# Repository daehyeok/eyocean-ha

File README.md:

# eyocean-ha

ESPHome-based Home Assistant integration for the **EYOCEAN LED Desk Lamp** (ASIN: B0BNDLND3Y) via 433.92 MHz RF control.

The EYOCEAN desk lamp uses a 433.92 MHz ASK/OOK remote with an **EV1527-based** protocol (32-bit fixed codes — extended from standard 24-bit EV1527, no rolling code). This project replaces the physical remote with an ESP32 + CC1101 transceiver, giving full Home Assistant control.

## Hardware

| Component                          | Purpose         |
| ---------------------------------- | --------------- |
| ESP32-S3 DevKit                    | Microcontroller |
| CC1101 433MHz module (SMA antenna) | RF transceiver  |
| Dupont wires                       | Wiring          |
| USB-C cable + power adapter        | Power           |

An ESP32-S3 SuperMini can instead sit on the [carrier board](#carrier-board--enclosure-esp32-s3-supermini),
which replaces the Dupont wires and fits a 3D-printed case.

### Wiring (ESP32-S3)

```
ESP32-S3          CC1101
─────────         ──────
GPIO9  (CLK)  →   SCK
GPIO10 (MOSI) →   MOSI
GPIO11 (MISO) →   MISO
GPIO12 (CS)   →   CSN
GPIO13 (TX)   →   GDO0
GPIO14 (RX)   →   GDO2
3.3V          →   VCC
GND           →   GND
```

### Wiring (ESP32-C3 SuperMini)

```
ESP32-C3          CC1101
─────────         ──────
GPIO4  (SCK)  →   SCK
GPIO10 (MOSI) →   MOSI
GPIO3  (MISO) →   MISO
GPIO7  (CS)   →   CSN
GPIO1  (TX)   →   GDO0
GPIO2  (RX)   →   GDO2
3.3V          →   VCC
GND           →   GND
```

> [!CAUTION]
> CC1101 runs on 3.3V only. Do NOT connect to 5V.

### Carrier board + enclosure (ESP32-S3 SuperMini)

Instead of Dupont wires you can solder both modules straight onto a small
carrier PCB (`pcb/`) and close it in a 3D-printed box (`cad/`):

| Part                                                 | Qty | Notes                                                    |
| ---------------------------------------------------- | --- | -------------------------------------------------------- |
| Carrier PCB, 53.5 × 32 mm, 2 layers, 1.6 mm          | 1   | `pcb/production/eyocean_carrier_jlcpcb.zip`              |
| ESP32-S3 SuperMini                                   | 1   | male headers pointing down, soldered to the carrier      |
| CC1101 433 MHz module with SMA (see `CC1101_specs/`) | 1   | its male 2×4 header soldered to the carrier              |
| 10 µF capacitor, 0603, X5R, 10 V (LCSC C19702)       | 1   | on the back; CC1101 VDD bulk (module has its own 100 nF) |
| M2 × 16 flat-head (countersunk) bolt                 | 4   | flush; M2 × 14 / × 12 also work (counterbore)            |
| M2 hex nut                                           | 4   | captured under the base                                  |
| 433 MHz SMA antenna                                  | 1   | screws on outside the case                               |

No sockets are used: each module rests on its header's plastic spacer,
2.5 mm above the carrier. The CC1101's edge lines up with the board's SMA
end so the SMA barrel hangs past it.

The carrier routes the CC1101 to the SuperMini's **left** header column
(TX, RX, GPIO1–7). 3V3 and GND come from the right column; 5V is never
connected. GPIO3 is left free because it is a strapping / VBUS-sense pin on
some SuperMini clones.

| CC1101 pin | Signal    | SuperMini pin | ESPHome substitution |
| ---------- | --------- | ------------- | -------------------- |
| 1          | GND       | GND           | –                    |
| 2          | VDD       | 3V3           | –                    |
| 3          | GDO0      | GPIO7         | `pin_tx`             |
| 4          | CSN       | GPIO6         | `pin_cs`             |
| 5          | SCK       | GPIO5         | `pin_sck`            |
| 6          | MOSI      | GPIO4         | `pin_mosi`           |
| 7          | MISO/GDO1 | GPIO2         | `pin_miso`           |
| 8          | GDO2      | GPIO1         | `pin_rx`             |

`esphome/pzloz-carrier.yaml` already uses these pins. It includes
`eyocean-rf.yaml` and only overrides the name, the pins and your remote
codes, so it works for EYOCEAN lamps too.

**PCB.** The KiCad 10 project is generated from `pcb/scripts/board_def.py`
(one table for pins, placement and nets). `pcb/scripts/build.sh`
regenerates the schematic and the board, runs ERC and DRC (with schematic
parity) and exports the JLCPCB Gerber zip, SVGs, a 3D render and a STEP
model to `pcb/production/`. The board keeps copper out from under the
SuperMini's chip antenna (the far end, opposite the USB-C port).

**Enclosure.** A base and a lid, 60.5 × 37 × 18.1 mm, split on the SMA
axis. It has a USB-C opening, an SMA U-slot, WiFi slots over the antenna,
and four flush M2 × 16 bolts into hex nuts under the base. See
**[`cad/README.md`](cad/README.md)** for the build guide: prerequisites,
how every height is calculated, what to measure on your parts, export
commands, print settings and assembly.

```bash
git submodule update --init   # BOSL2
cad/export.sh                 # -> cad/export/enclosure_{bottom,lid}.{stl,3mf}
```

Assembly in short:

1. Solder the SuperMini (USB-C at the board edge) and
   the CC1101 (SMA end flush with the board edge), with header spacers flat
   on the carrier.
2. Trim the pin tails under the board to ≤ 2.5 mm, then solder the 10 µF
   capacitor on the back (it sits in the 3.5 mm gap above the case floor).
3. Drop the board into the base. The SMA thread goes into the U-slot.
4. Close the lid, push an M2 nut into each hex pocket under the base, and
   tighten the four bolts from the top.
5. Screw the 433 MHz antenna onto the SMA.

## Protocol Details

| Parameter       | Value                                                     |
| --------------- | --------------------------------------------------------- |
| Frequency       | 433.92 MHz                                                |
| Modulation      | ASK/OOK                                                   |
| Protocol        | EV1527-based (32-bit)                                     |
| Frame structure | 16-bit fixed prefix + 8-bit button code + 8-bit XOR check |
| Security        | Fixed code (no rolling)                                   |
| FCC ID          | 2BD2C-ZZ02DY01007                                         |

### Decoded Remote Codes

The EYOCEAN remote uses a **32-bit** frame (not standard 24-bit EV1527). All 32 bits are required — the lamp ignores truncated 24-bit frames.

**Frame structure:**

| Byte | Content       | Varies per remote?              |
| ---- | ------------- | ------------------------------- |
| 0-1  | Remote ID     | **yes** — per-remote address    |
| 2    | Function code | no — same across remotes        |
| 3    | Checksum      | `byte2 XOR key`, key per-remote |

```
code = (remote_id << 16) | (cmd << 8) | (cmd ^ xor_key)
```

The **function codes are shared across units** — only the 16-bit remote ID and the 8-bit XOR key are per-remote. This reproduces all 11 known codes from the two fully-decoded remotes below.

| Button            | Function code   |
| ----------------- | --------------- |
| Power On/Off      | `0x51`          |
| Brightness        | `0x5B`          |
| Color Temperature | `0x5A`          |
| Reading Mode      | `0x49`          |
| Night Light       | `0x41` / `0x4D` |
| Timer Function    | `0x4D` / `0x41` |

`0x41` and `0x4D` swap meaning between models: 5-button remotes (no timer) use `0x41` for night light, and the two 6-button remotes reported so far disagree with each other — see [#3](https://github.com/bl4ko/eyocean-ha/issues/3). If those two buttons act swapped on your lamp, exchange `cmd_night_light` / `cmd_timer` in the config.

**Known remotes:**

| Lamp                                | Remote ID | XOR key | Source                                                    |
| ----------------------------------- | --------- | ------- | --------------------------------------------------------- |
| EYOCEAN (ASIN B0BNDLND3Y), 5 buttons | `0xBAD1`  | `0x4E`  | this repo                                                  |
| EYOCEAN CLED-2600C (ASIN B09ZHYNYB9), 6 buttons | `0xDCCF` | `0x76` | [#3](https://github.com/bl4ko/eyocean-ha/issues/3) |
| Pzloz, 6 buttons                    | ?         | ?       | [#1](https://github.com/bl4ko/eyocean-ha/issues/1) (partial) |

The XOR key is not derivable from the remote ID with the data available (`0xBAD1`→`0x4E`, `0xDCCF`→`0x76`); treat it as an independent per-remote value.

> [!IMPORTANT]
> **You still need to capture one button from your own remote** to learn its ID and XOR key — but only one. Capture any button, then read the ID off bytes 0-1 and compute the key as `byte2 XOR byte3`; the other buttons follow from the formula. See [Capturing Your Own Codes](#capturing-your-own-codes). Standard 24-bit EV1527 decoders (Flipper Zero, rtl_433) only show the first 24 bits — you must capture raw data and decode all 32 bits.

## Installation

### 1. Configure

Everything unit-specific lives in the `substitutions:` block at the top of `esphome/eyocean-rf.yaml`:

```yaml
substitutions:
  board: esp32-s3-devkitc-1
  pin_sck: GPIO9
  pin_mosi: GPIO10
  pin_miso: GPIO11
  pin_cs: GPIO12
  pin_tx: GPIO13
  pin_rx: GPIO14

  remote_id: "0xBAD1"
  xor_key: "0x4E"
  cmd_night_light: "0x41"
  cmd_timer: "0x4D"
```

For an ESP32-C3 SuperMini, swap in:

```yaml
  board: esp32-c3-devkitm-1
  pin_sck: GPIO4
  pin_mosi: GPIO10
  pin_miso: GPIO3
  pin_cs: GPIO7
  pin_tx: GPIO1
  pin_rx: GPIO2
```

Set `remote_id` and `xor_key` from your own capture — see [Capturing Your Own Codes](#capturing-your-own-codes).

### Pzloz desk lamp (6 buttons)

Pzloz lamps use the same 32-bit protocol and function codes. Flash
`esphome/pzloz-carrier.yaml` (carrier board) or `eyocean-rf.yaml` (your own
wiring), then:

1. Press any button on the Pzloz remote and read the 32-bit frame that
   `remote_receiver` logs.
2. Set `remote_id` (bytes 0–1) and `xor_key` (byte 2 XOR byte 3) in the
   `substitutions:` block, then flash again.
3. All six buttons appear in Home Assistant: Power, Brightness, Color
   Temperature, Reading Mode, Night Light and Timer Function. If Night Light
   and Timer act swapped, exchange `cmd_night_light` and `cmd_timer`.

Please report your Pzloz remote ID and XOR key in
[#1](https://github.com/bl4ko/eyocean-ha/issues/1) so the table above can
be filled in.

### 2. Flash ESPHome

```bash
pip install esphome
esphome run esphome/eyocean-rf.yaml
```

### 3. Add to Home Assistant

The device auto-discovers via ESPHome integration. Go to **Settings → Devices & Services → ESPHome** and adopt the device.

### 4. Place Near Lamp

The ESP32+CC1101 needs RF line-of-sight to the lamp's receiver. Place within ~5m for reliable operation.

## State Management

The lamp is **receive-only** — it has no back-channel to report its state.

## Capturing Your Own Codes

You only need **one** button — the rest follow from the formula. The protocol uses **32-bit frames**; standard EV1527 decoders only show 24 bits, so you must capture raw data.

1. **Option A — Flipper Zero**: Sub-GHz → Read → press the button → save the `.sub`
2. **Option B — ESP32+CC1101**: this config already includes `remote_receiver` with `dump: all` — flash it, press the button, read the logs
3. **Option C — RTL-SDR**: `rtl_433` in raw mode

Take the 32-bit frame and split it:

```
0xDCCF5127
  ├─ 0xDCCF  → remote_id
  ├─ 0x51    → function code (Power, confirms you decoded it right)
  └─ 0x27    → xor_key = 0x51 XOR 0x27 = 0x76
```

Put `remote_id` and `xor_key` in the `substitutions:` block. If the function code doesn't match the [table above](#decoded-remote-codes), your remote is a new variant — please open an issue.

## How It Works

```
┌───────────────┐    433.92 MHz    ┌───────────────┐
│ ESP32+CC1101  │ ──── RF ────→    │ EYOCEAN Lamp  │
│  (ESPHome)    │                  │  (receiver)   │
└──────┬────────┘                  └───────────────┘
       │ WiFi
       ▼
┌────────────────┐
│ Home Assistant │
│  (dashboard)   │
└────────────────┘
```

The ESP32 connects to your WiFi and exposes entities to Home Assistant. When you toggle a switch in HA, ESPHome transmits the corresponding EV1527 code via the CC1101 at 433.92 MHz — exactly as the original remote would.

## Contributing

Got a working setup on your EYOCEAN (or compatible, e.g. Pzloz) lamp? Open a PR or issue with your remote ID, XOR key, model number and button count — more data points help map the protocol across units and brands, and may yet reveal how the XOR key is derived.

## License

MIT

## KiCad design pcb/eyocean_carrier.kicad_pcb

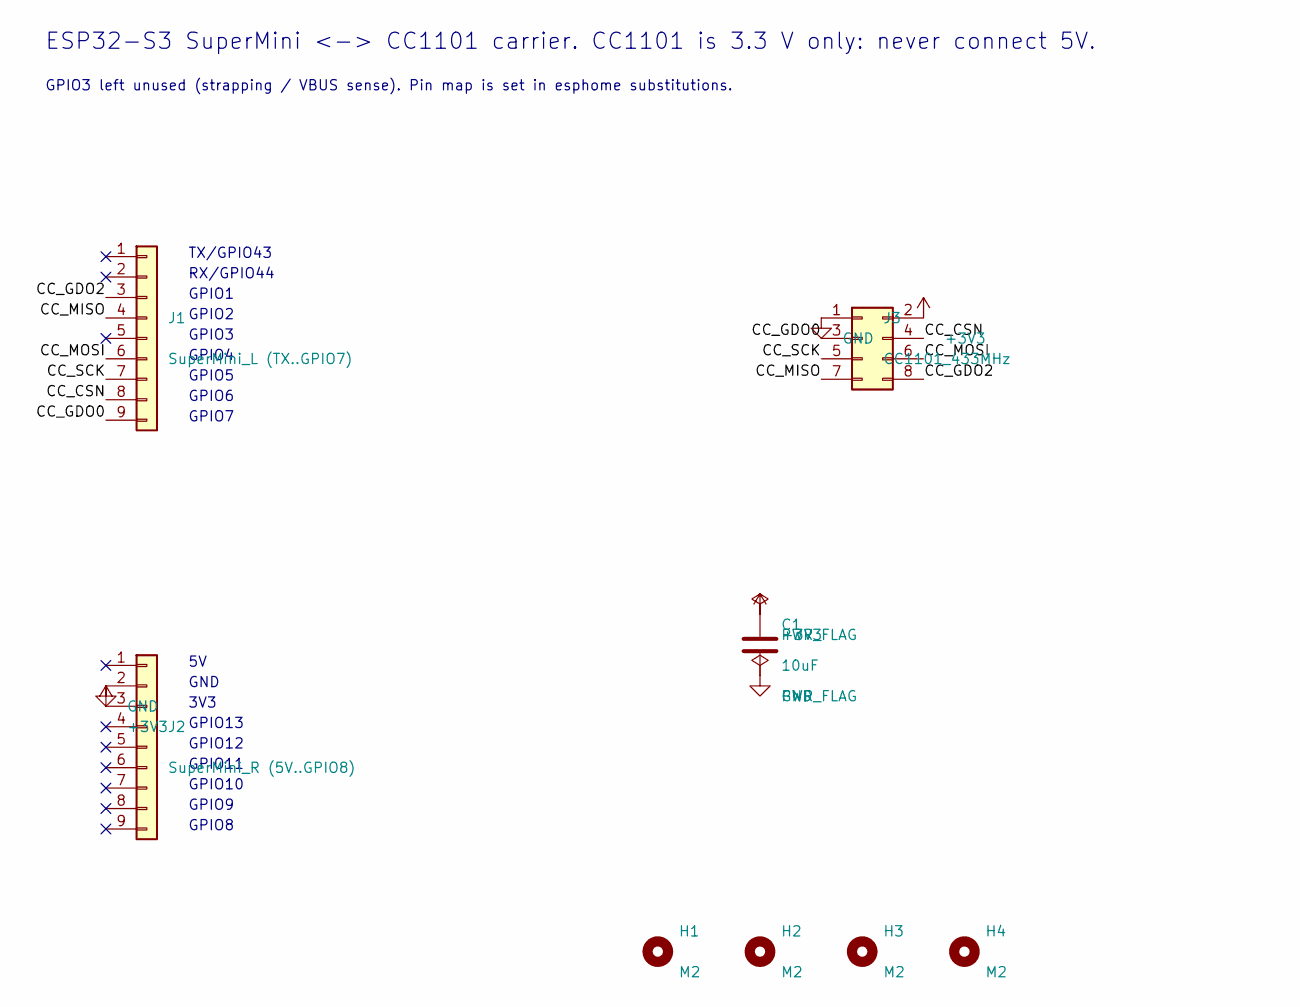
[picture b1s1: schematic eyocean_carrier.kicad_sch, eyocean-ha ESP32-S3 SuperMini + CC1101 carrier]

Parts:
C1: 10uF; C_0603_1608Metric_Pad1.08x0.95mm_HandSolder
H1, H2, H3, H4: M2; MountingHole_2.2mm_M2
J1: SuperMini_L (TX..GPIO7); PinSocket_1x09_P2.54mm_Vertical
J2: SuperMini_R (5V..GPIO8); PinSocket_1x09_P2.54mm_Vertical
J3: CC1101_433MHz; CC1101_Socket_2x04_P2.54mm_TopView

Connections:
+3V3: C1.1, J2.3, J3.2
/CC_CSN: J1.8, J3.4
/CC_GDO0: J1.9, J3.3
/CC_GDO2: J1.3, J3.8
/CC_MISO: J1.4, J3.7
/CC_MOSI: J1.6, J3.6
/CC_SCK: J1.7, J3.5
GND: C1.2, J2.2, J3.1

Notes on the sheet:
TX/GPIO43
RX/GPIO44
GPIO1
GPIO2
GPIO3
GPIO4
GPIO5
GPIO6
GPIO7
GND
3V3
GPIO13
GPIO12
GPIO11
GPIO10
GPIO9
GPIO8
ESP32-S3 SuperMini <-> CC1101 carrier. CC1101 is 3.3 V only: never connect 5V.
GPIO3 left unused (strapping / VBUS sense). Pin map is set in esphome substitutions.

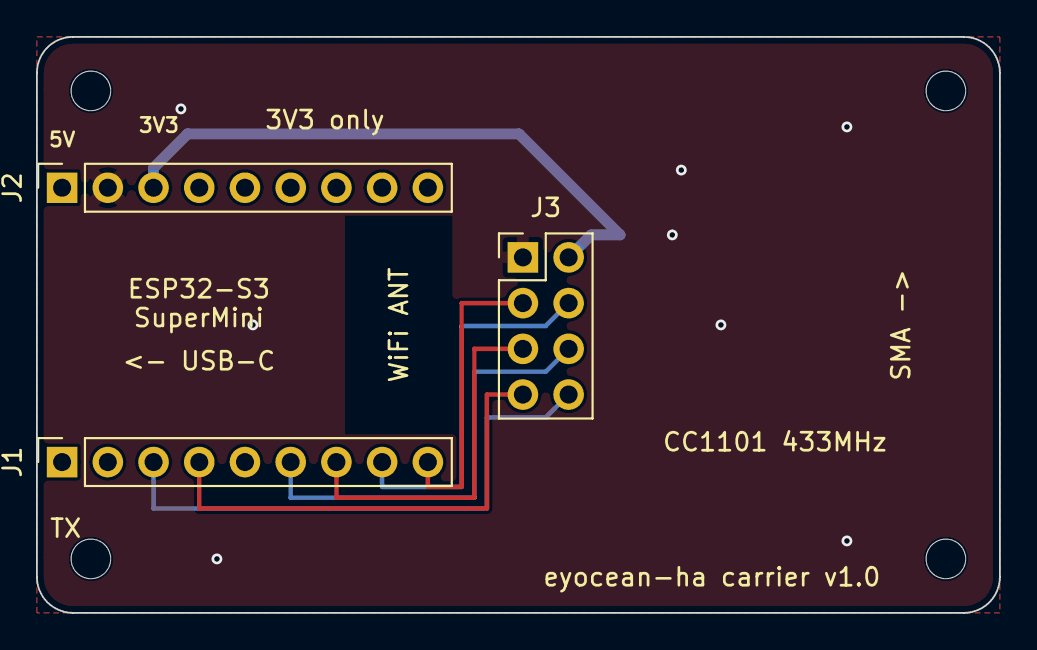
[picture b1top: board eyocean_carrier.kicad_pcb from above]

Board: 2 copper layers, 53.5 x 32.0 mm, 8 parts (1 on the bottom side), 8 nets.
